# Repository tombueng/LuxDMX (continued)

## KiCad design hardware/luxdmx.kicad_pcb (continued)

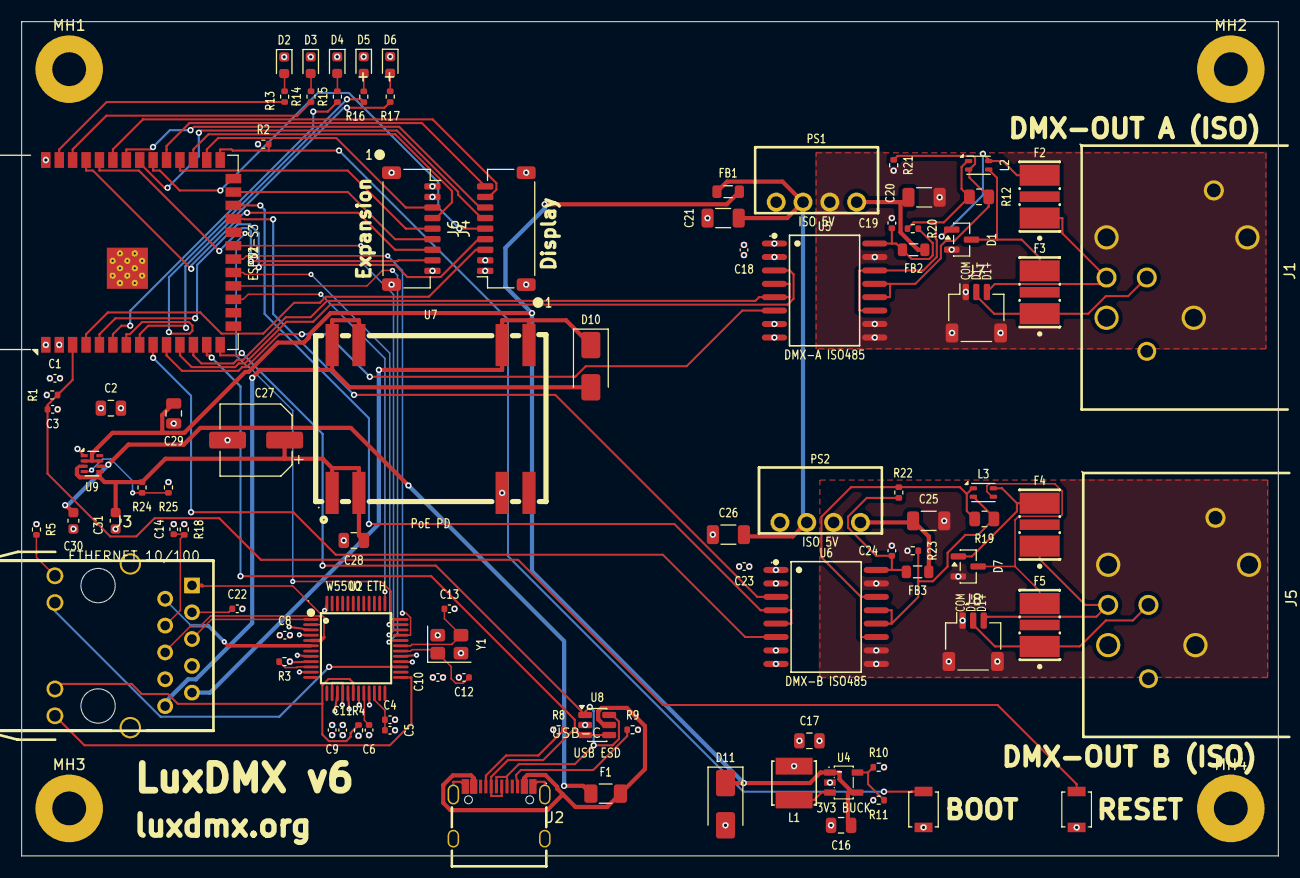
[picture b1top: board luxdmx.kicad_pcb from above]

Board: 4 copper layers, 119.0 x 79.0 mm, 97 parts (0 on the bottom side), 86 nets.

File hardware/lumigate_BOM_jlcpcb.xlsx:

Comment | Designator | Footprint | LCSC Part #
100nF 0402 | C1,C5,C8,C9,C10,C11,C14,C15,C18,C19,C22,C23,C24 | C_0402_1005Metric | C1525
10uF 0805 | C2,C28 | C_0805_2012Metric | C15850
1uF 0402 (EN power-on RC) | C3,C4 | C_0402_1005Metric | C52923
4.7uF 0402 | C6 | C_0402_1005Metric | C23733
22pF 0402 | C12,C13 | C_0402_1005Metric | C1555
22uF 0805 | C16,C17,C29 | C_0805_2012Metric | C45783
10uF 1206 | C20,C21,C25,C26 | C_1206_3216Metric | C13585
100uF 25V SMD electrolytic (PoE output bulk) | C27 | CP_Elec_6.3x7.7 | C970685
1uF 0603 (TPS2116 VIN1 input cap) | C30,C31 | C_0603_1608Metric | C15849
SM712 TVS SOT-23 | D1,D7 | SOT-23 | C404012
LED red 0603 | D2 | LED_0603_1608Metric | C2286
LED green 0603 KT-0603G | D3 | LED_0603_1608Metric | C12624
LED yellow 0603 NCD0603Y2 | D4 | LED_0603_1608Metric | C89811
LED blue 0603 KT-0603B | D5 | LED_0603_1608Metric | C2288
LED white 0603 | D6 | LED_0603_1608Metric | C2290
SMAJ58A TVS SMA (rectified-PoE surge clamp) | D10 | D_SMA | C110521
SMAJ5.0A TVS SMA (+5V transient clamp) | D11 | D_SMA | C151932
BSMD1206-150-16V 1.5A/16V resettable PPTC fuse (USB VBUS) | F1 | Fuse_1206_3216Metric | C883133
600R@100MHz ferrite bead 0805 (+5V to DMX DC-DC) | FB1,FB2,FB3 | L_0805_2012Metric | C139168
Neutrik NC5FAH XLR-5 female horizontal PCB (E1.11 DMX out) | J1,J5 | CONN-TH_NC5FAH | C368501
USB-C data (TYPE-C-31-M-12) | J2 | USB-C_SMD-TYPE-C-31-M-12_1 | C165948
RJ45 MagJack HY931147C PoE 10/100 (integrated rectifier + magnetics) | J3 | RJ45-TH_HY931147C | C91754
JST SH 1.0mm 9-pin SMD SM09B-SRSS-TB (optional display; pre-crimped cables) | J4,J6 | JST_SH_SM09B-SRSS-TB_1x09-1MP_P1.00mm_Horizontal | C160408
JST SH 1.0mm 3-pin SMD SM03B-SRSS-TB (DMX-A breakout) | J7,J8 | JST_SH_SM03B-SRSS-TB_1x03-1MP_P1.00mm_Horizontal | C160403
2.2uH power inductor (CKCS4030) | L1 | IND-SMD_L4.0-W4.0 | C354584
ACM2012-201-2P common-mode choke (DMX-A pair) | L2,L3 | L_CommonModeChoke_Coilank_ACM2012 | C383338
B0505S-1W iso DC-DC (EVISUN) | PS1,PS2 | PWRM-TH_B0505S-1W | C7465127
MMBT3904 SOT-23 | Q1,Q2 | SOT-23 | C20526
10k 0402 | R1,R2,R6,R7,R11 | R_0402_1005Metric | C25744
12k 0402 W5500 EXRES1 (12.4k spec OOS at LCSC; 12k within 100BASE-TX +-5%) | R3 | R_0402_1005Metric | C25752
330R 0402 | R4,R5 | R_0402_1005Metric | C25104
5k1 0402 | R8,R9 | R_0402_1005Metric | C25905
45.3k 0402 1% (buck FB top -> 3.32V) | R10 | R_0402_1005Metric | C137977
120R 0805 (DMX-A termination) | R12,R19 | R_0805_2012Metric | C17437
1k 0402 | R13,R15 | R_0402_1005Metric | C11702
150R 0402 | R14,R16,R17 | R_0402_1005Metric | C25082
49.9R 1% 0402 W5500 TX center-tap bias | R18 | R_0402_1005Metric | C25120
tact sw B3U-1000P | SW1,SW2 | SW_SPST_B3U-1000P | C231329
ESP32-S3-WROOM-1-N8 (8MB) | U1 | ESP32-S3-WROOM-1 | C2913198
W5500 SPI Ethernet | U2 | LQFP-48_L7.0-W7.0-P0.50-LS9.0-BL | C32843
CH340C USB-UART | U3 | SOP-16_L10.0-W3.9-P1.27-LS6.0-BL | C84681
SY8089 buck 5->3.3V | U4 | SOT-23-5_L3.0-W1.7-P0.95-LS2.8-BR | C78988
ISO3086DWR isolated RS-485 | U5,U6 | SOIC-16_L10.3-W7.5-P1.27-LS10.3-BL | C183095
DP9900M-5V PoE PD + isolated DC-DC module (802.3af) | U7 | PWRM-SMD_DP9900M-5V | C5380106
USBLC6-2SC6 USB ESD/TVS array (SOT-23-6) | U8 | SOT-23-6 | C7519
TPS2116DRLR ideal-diode power mux (USB/PoE 5V OR-ing) | U9 | SOT-583-8 | C3235557
25MHz crystal 2520 | Y1 | Crystal_SMD_2520-4Pin_2.5x2.0mm | C2981622

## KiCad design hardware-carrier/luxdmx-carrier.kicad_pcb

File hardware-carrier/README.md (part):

# LuxDMX carrier board

A 2-layer PCB for off-the-shelf modules: an ESP32-S3 dev board, up to three RS-485 modules, a
W5500 Ethernet module and an OLED. Encoder and two buttons sit on the board itself. DMX and RDM on
up to three ports, WS281x pixels on up to five.

The board is built and runs on the bench; most firmware testing happens on it.

| | |
|---|---|
| Board | 100 x 80 mm, 2 layers, 1 oz copper, no mounting holes |
| DMX / RDM | up to 3 ports, one MAX3485 module each, direction pin driven, **not isolated** |
| Pixels | up to 5 WS281x ports, buffered to 5 V by a 74HCT541 |
| Network | WiFi, or wired with a W5500 module |
| Logic supply | USB-C on the ESP module, external 5 V, or a buck module off the pixel rail |
| Pixel supply | 12 or 24 V screw terminal, fused on the board, 9.8 A max |
| UI | 1.3" SH1106 OLED, EC11 encoder with push switch, two buttons |
| Firmware | **ESP32-S3 + PSRAM** image, then the **LuxDMX Carrier** board in `/config` |

Contents: [Modules](#modules) · [Pin map](#pin-map) · [Power](#power) · [DMX ports](#dmx-ports) ·
[Pixel ports](#pixel-ports) · [All parts](#all-parts) · [Build levels](#build-levels) ·
[Ordering](#ordering) · [Assembly](#assembly) · [Before you power it](#before-you-power-it) ·
[Firmware](#firmware) · [Known issues](#known-issues)

## Modules

These are the units the bench board is built with. Other sellers' modules work if pinout and
size match, check both before buying.

| Slot | Module | Pins | Notes |
|---|---|---|---|
| MCU | ESP32-S3-DevKitC-1 clone, **WROOM-1-N16R8**, dual USB-C (Binghe, Amazon.de B0D6B2CYNW). Search `ESP32-S3-DevKitC-1 N16R8` | 2 x 22, official DevKitC-1 pin order | 57.5 x 27.9 mm, rows **25.40 mm** apart. Espressif's own DevKitC-1 has 22.86 mm rows and does **not** fit. Compare the seller's drawing against the footprint before buying |
| RS-485, x3 | MAX3485 module, silk `RS485 V2.01` (RAKSTORE, Amazon.de B0C2HRQ393). Search `MAX3485 TTL to RS485 module 3.3V` | left: GND / A / B<br>right: EN / VCC / RXD / TXD / GND | 3.3 V, not isolated. EN is DE and RE tied together, one GPIO per port, which is what RDM needs. A module without EN can't do RDM. RXD is the module's input (DI), TXD its output (RO); the board crosses them |
| Ethernet | USR-ES1 (W5500). Search `USR-ES1 W5500` | 2 x 6, rows 20.32 mm | 3.3 V only, no LDO on the module. About 132 mA typical. The single-row 8-pin W5500 boards are a different module |
| Display | 1.3" OLED, SH1106, 128 x 64, I2C. Search `1.3 inch OLED I2C SH1106` | board pads 1-4: GND / 3V3 / SCL / SDA | Sits on a 1x4 female socket, 8.5 mm tall, which lifts the glass 10.9 mm clear of the modules. Sold with VCC and GND in either order, read the module's silk |
| Encoder | bare EC11 with push switch, 20 mm D-shaft (the part inside a KY-040) | soldered to the board | GPIO pull-ups are internal, the KY-040's three 10k aren't needed |
| Buttons, x2 | 6 x 6 mm tact switch | soldered to the board | Plunger 5 to 30 mm on the same land. The encoder shaft stands 20 mm, so 30 mm reaches the same front panel |

## Pin map

From the board's nets. Picking **LuxDMX Carrier** in `/config` sets these.

| Function | GPIO |
|---|---|
| DMX 1 TX / RX / DE+RE | 17 / 18 / 16 |
| DMX 2 TX / RX / DE+RE | 15 / 7 / 6 |
| DMX 3 TX / RX / DE+RE | 5 / 4 / 8 |
| W5500 SCLK / MOSI / MISO / CS / INT / RST | 12 / 11 / 13 / 10 / 14 / 9 |
| Pixel 1 / 2 / 3 / 4 / 5 data (before the buffer) | 38 / 39 / 40 / 47 / 48 |
| Display SDA / SCL | 1 / 2 |
| Encoder A / B / switch | 42 / 41 / 21 |
| Button 1 / 2 (to GND) | 3 / 46 |
| `EXP` header | 3V3, GND, 47, 48, 43 (TX0), 44 (RX0) |

Not used, and not usable: 35/36/37 (octal PSRAM on any R8 module), 45 (flash voltage strap), 19/20
(USB), 0 (BOOT). IO48 also drives the module's own RGB LED, see [pixel ports](#pixel-ports).

## Power

### Rails

| Net | Comes from | Feeds |
|---|---|---|
| `+5V` | USB-C on the ESP module, **or** the `5V IN` header, **or** the buck module | ESP module 5V pin, 74HCT541 |
| `+3V3` | the ESP module's own regulator (800 mA on Espressif's design) | ESP32-S3, MAX3485 x3, W5500, OLED, DMX bias, pull-ups |
| `V_PIX_IN` | `12-24V IN` screw terminal | the fuse |
| `V_PIX` | after the fuse | 1000 µF, V+ on all five pixel terminals, buck module input |
| `GND` | one common ground | everything, including DMX pin 1 (the ports are not isolated) |

The 3.3 V load with everything fitted is about 269 mA. The W5500 and WiFi don't run at the same time.

No ORing diodes between the three 5 V sources: **one at a time**. With the buck fitted, don't plug
in USB while the 12/24 V is on.

### Supply setups

| Setup | Fit | Logic from | Pixel rail |
|---|---|---|---|
| DMX only, bench | nothing | USB-C | unused |
| DMX only, in a box | `5V IN` header | external 5 V | unused |
| Pixels, two supplies | 12-24V terminal, fuse, 1000 µF | USB or `5V IN` | 12/24 V |
| Pixels, one supply | as above + buck module | buck, from `V_PIX` | 12/24 V |
| 5 V pixels | 12-24V terminal, fuse, 1000 µF, no buck | USB or `5V IN` | 5 V |

### 5 V pixels and USB

**USB never reaches the pixel terminals.** `V+` on all five is `V_PIX`, and `V_PIX` only comes from
the `12-24V IN` terminal through the fuse. Neither USB nor `5V IN` is connected to it. With nothing on
that terminal the data is there, `/pixels.json` shows the port running at full frame rate, and the
strip stays dark.

**WS2812 and other 5 V pixels:** the 5 V goes into `12-24V IN`, despite the name. The rail doesn't
care about the voltage. Leave the buck out, it can't make 5 V out of 5 V.

**One 5 V supply for both:** bridge `5V IN` to `12-24V IN`. That's how the bench carrier runs. The
bridge also ties the logic to whatever is on that terminal, so take it off before anything above 5 V
gets near the board, and leave USB unplugged while it's on (one 5 V source at a time).

**USB may not even reach `+5V`.** The pixel buffer runs on `+5V`, and USB only gets there through the
module's 5V pin. On some S3 modules that pin isn't connected to USB until the `IN-OUT` solder pads are
bridged. We haven't measured this on a module yet, but the bench carrier points that way: on USB, even
with `5V IN` bridged to `12-24V IN`, its pixels stayed dark, and a real 5 V supply on that bridge lit
them. If you run from USB, check for 5 V on `5V IN` with a meter. If it's missing, the ESP runs and
every pixel port is silent, because the buffer has no supply.

### Fuse

Exactly one of these three:

| Option | Part | When |
|---|---|---|
| Polyfuse | Bourns MF-R500 (30 V, 5 A hold, 10 A trip), LCSC C208489 | default. Resets itself after cooling |
| Blade fuse | Keystone 3568 holder, MINI blade fuses (ATM, Littelfuse 297/997) | you'd rather swap a fuse. Not ATO/ATC, those are twice as wide |
| Solder bridge | pad pair on the back, inside the polyfuse footprint | the supply lead already has a fuse |

Polyfuse land: three holes, 5.08 mm (middle, MF-R110 to MF-R400, up to 4 A) and 10.2 mm (right,
MF-R500, up to 9 A). Use **30 V** parts only. MF-RHT, MF-RG and anything else rated 16 V is out of
rating at 24 V the moment it trips. MF-R900 (24 mm body) hits the 1000 µF can. Equivalents to the
MF-R500: ECE RB500-30, Littelfuse RUEF500. Full list in [`production/BOM.md`](production/BOM.md).

Never polyfuse and bridge together.

### Buck module

MP1584EN step-down module. Input max **28 V**, so a 24 V supply must not idle above that. **Set it to
5.0 V before soldering it in**: they ship with the trimmer anywhere, and 12 V on `+5V` kills the ESP32,
the W5500 and the display. Input is `V_PIX`, so it sits behind the fuse.

The land is four 12 x 5 mm pads with a solder-mask grid (7 x 3 windows of 1.1 mm), so modules from
22 x 18 to 30 x 18 mm land. LM2596 modules (43 x 21 mm) do not fit.

### Current rating

The pixel supply runs as 4.8 mm tracks from the inlet through the fuse along the terminal row. Each
output gets the full width and its own 4.8 mm GND return.

| 1 oz copper | 10 K rise | 20 K rise | at 24 V |
|---|---:|---:|---:|
| Pixel rail, fuse to the outputs | 7.2 A | **9.8 A** | 170 - 235 W |
| Pixel rail, inlet to the fuse | 7.3 A | 9.9 A | |
| Any single output | 7.2 A | 9.8 A | |
| GND return per output | 7.4 A | 10.1 A | |
| GND pour overall | 46.3 A | 62.8 A | |

- 10 K: board stays hand-warm. 20 K: fine for FR4, more current. Neither is a safety limit.
- All five ports in use: about 2 A each. A 5 m WS2815 run is about 5 A at full white.
- More than that: inject power at the strip.
- The polyfuse bridge pads limit a fuse-less build to 8.8 A. Bridge the through-holes with a wire for more.
- The bulk cap and buck hang off 2.0 mm spurs (5.3 A), they aren't load paths.

### Decoupling

| Where | Parts |
|---|---|
| 3.3 V at the ESP module | 100 nF + 22 µF |
| W5500, under the module on the back | 100 nF / 1 µF / 22 µF, smallest closest to its 3V3 pin |
| Pixel rail | 1000 µF 35 V, 13 mm can, 5.0 mm pitch |

The W5500 set matters: the 3.3 V reaches it through 62 mm of 0.60 mm track (about 62 nH), so the
local 22 µF is what holds the rail when the PHY steps its load.

## DMX ports

Per port, on the board:

| Part | Connection | Purpose |
|---|---|---|
| MAX3485 module | EN, DI, RO from the pin map | transceiver, 3.3 V |
| 10k | DE+RE to GND | driver off, receiver on while the ESP boots. Without it the driver can key the bus before firmware runs |
| 120 Ω | A to B | termination. Only at the **end** of the bus, and only if the module doesn't already have one |
| 330 Ω | A to 3.3 V | fail-safe bias |
| 330 Ω | B to GND | fail-safe bias, always as a pair with the one above |
| 2 x TVS | A to GND, B to GND | surge clamp for ports that leave the box |
| 3-pin header | 1 GND, 2 B, 3 A | to XLR pin 1 / 2 / 3 |

Bias: RS-485 wants more than 200 mV idle. 330 Ω gives 508 mV with one terminator and 275 mV with two.
270 to 390 Ω are fine, 430 and 470 Ω marginal, 560 Ω and up not enough. Fit it once per bus. Many
MAX3485 modules already carry 120 Ω and bias resistors; check before adding a second set.

TVS: SMF12CA (SOD-123FL, 200 W), or SMAJ12CA (SMA, 400 W). 12 V standoff so it stays off at the
+12 V common mode RS-485 allows, 14.7 V breakdown, 19.9 V clamp at 10 A. A varistor is no
substitute, it clamps around 40 V.

Header: 2.54 mm pitch, 1.20 mm holes. Takes a pin header or a 2.54 mm screw terminal (Phoenix
MPT 0,5/3-2,54, TE 282834-3, Xinya XY308-2.54-3P).

**Not isolated.** DMX GND is board GND. Fine for a desk or a small rig. Use an isolated RS-485
module on a separate build if you need it.

## Pixel ports

```
GPIO 38/39/40/47/48 ── 74HCT541 (5 V) ── 330 Ω ── terminal DATA
                                         V_PIX ── terminal V+
                                           GND ── terminal GND
```

**The buffer is required for pixels.** WS281x need 0.7 x VDD = 3.5 V as logic high on a 5 V strip
input; the S3 gives 3.3 V. Without the buffer nothing reaches the terminals at all, they hang off its
outputs.

### The buffer chip

`74HCT541D,653` (Nexperia), LCSC C547781, about 0.42 EUR. VCC on `+5V`, both output enables tied to
GND, inputs A1 to A5 used, A6 to A8 (pins 7 to 9) tied to GND by a track to pin 10.

Two things decide the part:

1. **The T.** HCT, AHCT and ACT have TTL input thresholds (VIH 2.0 V), so 3.3 V switches them on a
   5 V supply. HC, AHC and AC need 3.5 V and don't switch reliably.
2. **The package.** The land is SOIC-20W: 1.27 mm pitch, rows 10.10 mm apart, pads extended 0.80 mm
   for a soldering iron.

| Fits | Doesn't fit |
|---|---|
| 74HCT541D (Nexperia) | 74HC541, 74AHC541, 74AC541: CMOS thresholds |
| 74AHCT541D (Nexperia) | 74HCT540 / 74AHCT540: inverting, same pinout |
| SN74AHCT541DW, SN74HCT541DW (TI) | 74HCT244: different pinout |
| CD74ACT541M (TI) | `...541PW` (TSSOP 0.65 mm), what LCSC stocks most of |
| | `...541DB`, `...541DGS`, `...541RKS`, `SN74AHCT541NS` (narrow SO-20), DIP |
| | 74LVC541A: can't output 5 V |

### Series resistors

330 Ω per port at the buffer output. The buffer switches in 3 to 5 ns into unterminated strip wire;
that edge rings and overshoots into the first LED. A WS281x bit is 1.25 µs, so the slower edge
costs nothing. The resistor also limits current if DATA meets 5 V or GND. 220 to 470 Ω all work.
Same part as the DMX bias resistors.

### Terminals

5.08 mm, 3 pole: V+ / DATA / GND. Pads 3.60 x 3.30 mm on 1.30 mm holes. Fit the terminal or solder
the wire flat onto the pad.

### Things to know

- **IO48 is pixel port 5 and the module's RGB LED.** The carrier preset turns the status LED off.
  Not using port 5? Status LED back on at GPIO48, WS2812.
- **EXP header** brings out IO47 and IO48 **unbuffered** (3.3 V), alongside the buffered ports 4 and 5.
- **5 V strip works.** The rail is a pass-through and doesn't care about voltage, but 5 V strip needs
  about 3.5 times the current of 12 V strip for the same pixels. The limit here is amps, so the
  firmware defaults to WS2815 (12 V).
- **Driver:** the firmware uses the S3's LCD_CAM peripheral when PSRAM is there, which is why the
  carrier wants the PSRAM image. Chips, universes, power caps: [`docs/pixels.md`](../docs/pixels.md).

### Data line return path

341 mm of data line on the board. Two layers can't give every millimetre a ground plane underneath:

| | |
|---|---:|
| ground directly opposite, other layer | 60 % |
| ground alongside within 1.5 mm | 31 % |
| no ground within reach | 9 % |

The 9 % is 29 mm where the lines cross the supply bus, plus 8.5 mm under the ESP module. For a few
metres of strip this doesn't matter, and the series resistors cover it.

## All parts

Everything that can go on the board. Only the ESP module is mandatory. Small parts are 1206 in the
BOM, the lands take 0402 to 1206.

### Core

| Part | Value / part number | Fit when |
|---|---|---|
| ESP32-S3 module | DevKitC-1 clone, N16R8, 25.40 mm rows | always |

### DMX, per port (x3)

| Part | Value / part number | LCSC | Fit when |
|---|---|---|---|
| RS-485 module | MAX3485, with EN pin | | port used |
| DMX header | 1x3 pin header, or 2.54 mm screw terminal | | port used |
| `10k dir` | 10k, 1206W4F1002T5E | C17902 | port used |
| `120R term` | 120 Ω, 1206W4F1200T5E | | port at the end of the bus, module has none |
| `330R bias+`, `330R bias-` | 330 Ω, 1206W4J0331T5E | C25374 | port drives the bus, once per bus |
| `TVS bidir` x2 | SMF12CA, or SMAJ12CA | C353317 | port leaves the enclosure |

### Pixels

| Part | Value / part number | LCSC | Fit when |
|---|---|---|---|
| `74AHCT541 pixel buffer` | 74HCT541D,653, SO-20 300 mil | C547781 | at least one pixel port used |
| `330R PIX1..5` | 330 Ω, 1206W4J0331T5E | C25374 | that port used |
| `Pixel1..5` | KF128-5.08-3P screw terminal | C474953 | that port used |
| `12-24V IN` | KF128-5.08-2P screw terminal, 24 A | C474952 | any pixel port used |
| `1000uF 35V` | KM108M035J20RR0VH2FP0, D13 x 20 mm | C10749 | any pixel port used |
| Fuse | MF-R500 polyfuse **or** Keystone 3568 blade holder **or** solder bridge | C208489 (MF-R500) | any pixel port used, see [Fuse](#fuse) |

### Supply

| Part | Value / part number | Fit when |
|---|---|---|
| `5V Buck Converter` | MP1584EN module, set to 5.0 V first | logic from 12/24 V, no USB, no `5V IN` |
| `5V IN` | 1x2 pin header | external 5 V instead of USB |
| `100nF` | 100 nF X7R, CL31B104KBCNNNC (C24497) | recommended |
| `22uF 3V3 bulk` | 22 µF 6.3 V X5R, CL31A226MQHNNNE (C159757) | recommended |

### Network

| Part | Value / part number | LCSC | Fit when |
|---|---|---|---|
| `W5500 Ethernet Module` | USR-ES1 | | wired Ethernet |
| `10k ETH_CS pu` | 10k to 3.3 V | C17902 | W5500 fitted. Holds CS high while the GPIOs float during reset |
| `10k ETH_RST pu` | 10k to 3.3 V | C17902 | W5500 fitted. Without it the W5500 resets itself during boot |
| `100nF W5500` | 100 nF | C24497 | W5500 fitted |
| `1uF W5500` | 1 µF X7R, CL31B105KBHNNNE | C1848 | W5500 fitted |
| `22uF W5500` | 22 µF X5R | C159757 | W5500 fitted |

### Interface

| Part | Value / part number | Fit when |
|---|---|---|
| `Display` | 1.3" SH1106 I2C OLED on a 1x4 female socket, 8.5 mm | you want the display |
| `Encoder` | EC11 with push switch, 20 mm D-shaft | you want the on-unit menu |
| `Button 1`, `Button 2` | 6 x 6 mm tact switch, 30 mm plunger | you want the buttons |
| `EXP` | 1x6 pin header | you need spare pins |

LCSC small parts for a fully fitted board: about 2.80 EUR. Stock, prices, marketplace links and
search terms for every module: [`production/BOM.md`](production/BOM.md). Every position with its
side and fit condition: [`ASSEMBLY.md`](ASSEMBLY.md).

## Build levels

| Build | DMX | Pixels | Network | Fit |
|---|---|---|---|---|
| DMX only, USB powered | 1-3 | - | WiFi | ESP, RS-485 module + header + 10k per port, bias / termination / TVS as needed |
| DMX + LAN | 1-3 | - | W5500 | above + W5500, its two 10k and 100 nF / 1 µF / 22 µF |
| Pixels only | - | 1-5 | WiFi | ESP, buffer, 330 Ω + terminal per port, 1000 µF, inlet, fuse, buck or USB |
| Everything | 3 | 5 | W5500 | all of it, plus display, encoder, buttons |

## Ordering

- **PCB:** [`production/luxdmx-carrier-gerbers.zip`](production/), 2 layers, 1 oz, 1.6 mm, any fab
  (e.g. <https://cart.jlcpcb.com/quote>).
- **Small parts:** [`production/BOM-LCSC-upload.csv`](production/) goes straight into
  <https://www.lcsc.com/bom>. Also as `BOM.csv` / `BOM.xlsx`, and `BOM-TME.md` for TME.
- **Modules:** search terms and example links in [`production/BOM.md`](production/BOM.md). Links rot,
  search terms don't.

## Assembly

1. Back side first: all small parts sit under the modules.
2. Then the headers and sockets on the front.
3. Set the buck to 5.0 V, then solder it.
4. Plug in the modules.

Hand soldering only. Resistor and capacitor lands run 0.30 to 2.30 mm off centre, so 0402, 0603,
0805 and 1206 all land on copper (1210 overhangs in width). TVS lands go to 2.90 mm and take
SOD-123, SOD-123F, SOD-123FL, SMA and 1206. The lands are longer than the parts and nothing
self-aligns, so this board doesn't reflow.

## Before you power it

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
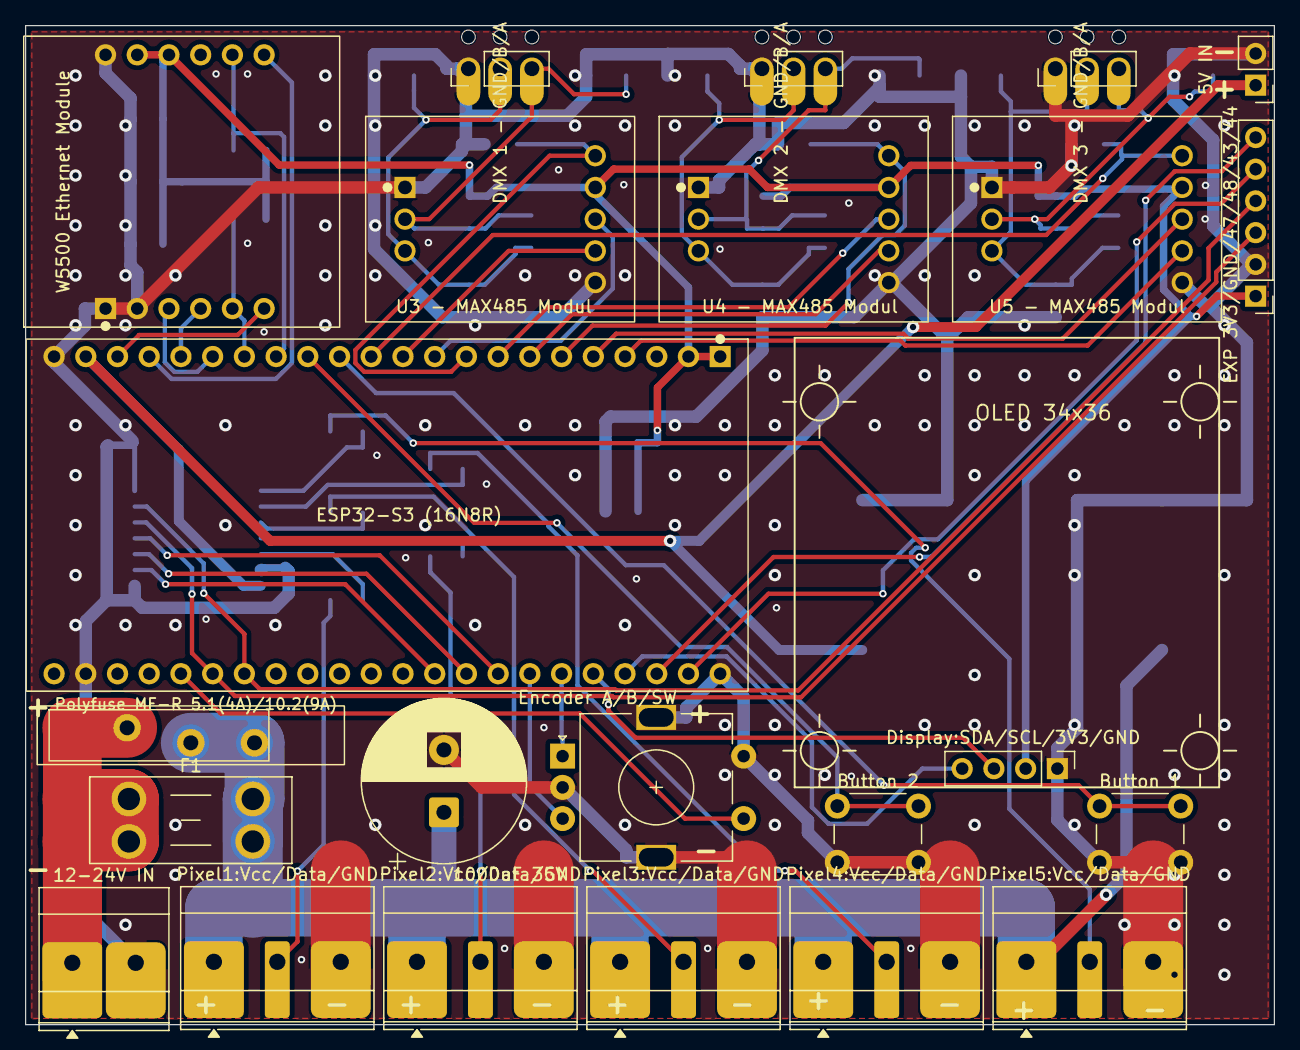
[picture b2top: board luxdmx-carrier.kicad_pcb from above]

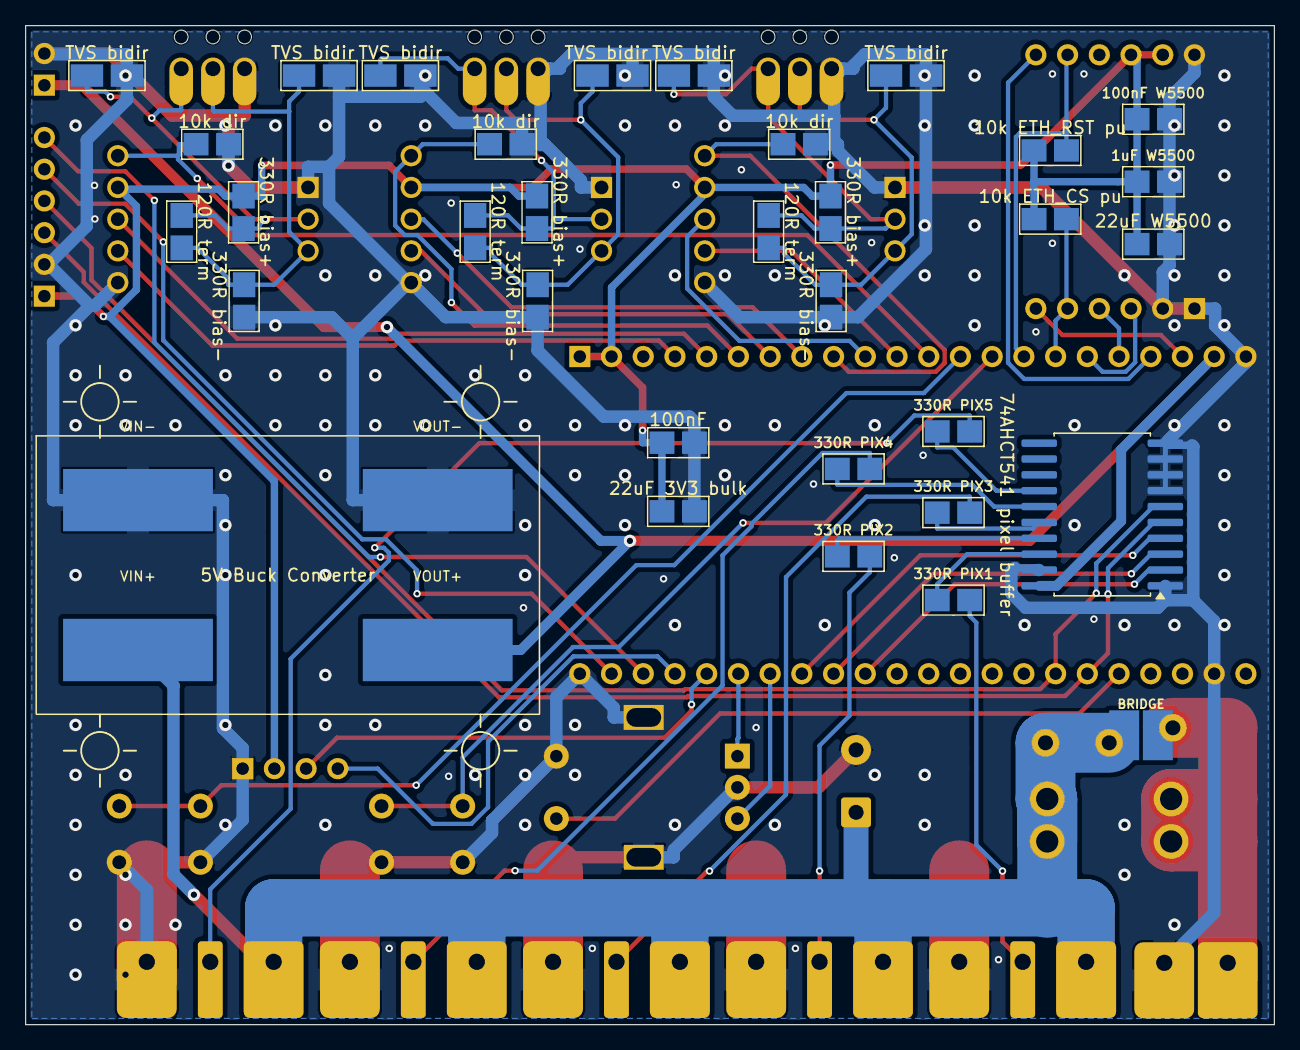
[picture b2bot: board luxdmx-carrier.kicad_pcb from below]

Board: 2 copper layers, 100.0 x 80.0 mm, 55 parts (32 on the bottom side), 50 nets.

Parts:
1uF W5500: 1uF; chip-universal
5V Buck Converter: 12-24V -> 5V buck; buck-module-universal
5V IN: 5V in; PinHeader_1x02_P2.54mm_Vertical
10k ETH_CS pu: 10k ETH_CS pu; chip-universal
10k ETH_RST pu: 10k ETH_RST pu; chip-universal
10k dir, 10k dir#2, 10k dir#3: 10k dir; chip-universal
12-24V IN: 12-24V IN 24A; terminal-1x02-P5.08-bigpad
22uF 3V3 bulk: 22uF 3V3 bulk; chip-universal
22uF W5500: 22uF W5500; chip-universal
74AHCT541 pixel buffer: 74AHCT541 pixel buffer; SOIC-20W_7.5x12.8mm_P1.27mm
100nF, 100nF W5500: 100nF; chip-universal
120R term, 120R term#2, 120R term#3: 120R term; chip-universal
330R PIX1, 330R PIX2, 330R PIX3, 330R PIX4, 330R PIX5: 330R pixel; chip-universal
330R bias+, 330R bias+#2, 330R bias+#3: 330R bias+; chip-universal
330R bias-, 330R bias-#2, 330R bias-#3: 330R bias-; chip-universal
1000uF 35V: 1000uF 35V; CP_Radial_D13.0mm_P5.00mm
Button 1, Button 2: Tact 6x6 H30; SW_PUSH_6mm
DMX 1 - GND/B/A: XLR1 1=shld 2=D- 3=D+; header-1x03-P2.54-terminal
DMX 2 - GND/B/A: XLR2 1=shld 2=D- 3=D+; header-1x03-P2.54-terminal
DMX 3 - GND/B/A: XLR3 1=shld 2=D- 3=D+; header-1x03-P2.54-terminal
Display:SDA/SCL/3V3/GND: OLED SDA/SCL/VCC/GND; PinHeader_1x04_P2.54mm_Vertical
ESP32-S3 (16N8R): ESP32-S3 N16R8; desk_binghe-esp32-s3-devkitc1-n16r8-usbc
EXP 3V3/GND/47/48/43/44: EXP 3V3/GND/47/48/43/44; PinHeader_1x06_P2.54mm_Vertical
Encoder A/B/SW: EC11; encoder-ec11-switch
F1: Blade fuse holder, alternative to the polyfuse; Fuseholder_Blade_Mini_Keystone_3568
Pixel1:Vcc/Data/GND: PIX1 V+/DATA/GND; terminal-1x03-P5.08-bigpad
Pixel2:Vcc/Data/GND: PIX2 V+/DATA/GND; terminal-1x03-P5.08-bigpad
Pixel3:Vcc/Data/GND: PIX3 V+/DATA/GND; terminal-1x03-P5.08-bigpad
Pixel4:Vcc/Data/GND: PIX4 V+/DATA/GND; terminal-1x03-P5.08-bigpad
Pixel5:Vcc/Data/GND: PIX5 V+/DATA/GND; terminal-1x03-P5.08-bigpad
Polyfuse MF-R 5.1(4A)/10.2(9A): MF-R 30V: links+mitte bis 4A, links+rechts bis 9A; polyfuse-dual-pitch
TVS bidir: TVS bidir; chip-universal-tvs
TVS bidir#2, TVS bidir#3, TVS bidir#4, TVS bidir#5, TVS bidir#6: TVS bidir; chip-universal-tvs
U3 - MAX485 Modul: MAX3485 DMX1; desk_rakstore-max3485
U4 - MAX485 Modul: MAX3485 DMX2; desk_rakstore-max3485
U5 - MAX485 Modul: MAX3485 DMX3; desk_rakstore-max3485
W5500 Ethernet Module: USR-ES1 W5500; usr-es1-w5500

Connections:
+3V3: 1uF W5500.1, 10k ETH_CS pu.1, 10k ETH_RST pu.1, 22uF 3V3 bulk.1, 22uF W5500.1, 100nF.1, 100nF W5500.1, 330R bias+.1, 330R bias+#2.1, 330R bias+#3.1, Display:SDA/SCL/3V3/GND.2, ESP32-S3 (16N8R).1, ESP32-S3 (16N8R).2, EXP 3V3/GND/47/48/43/44.1, U3 - MAX485 Modul.5, U4 - MAX485 Modul.5, U5 - MAX485 Modul.5, W5500 Ethernet Module.8, W5500 Ethernet Module.9
+5V: 5V Buck Converter.4, 5V IN.1, 74AHCT541 pixel buffer.20, ESP32-S3 (16N8R).21
BTN1: Button 1.1, ESP32-S3 (16N8R).13
BTN2: Button 2.1, ESP32-S3 (16N8R).14
DMX1_A: 120R term#2.1, 330R bias+#2.2, DMX 1 - GND/B/A.3, TVS bidir#3.1, U3 - MAX485 Modul.2
DMX1_B: 120R term#2.2, 330R bias-#2.1, DMX 1 - GND/B/A.2, TVS bidir#6.1, U3 - MAX485 Modul.3
DMX1_DIR: 10k dir.1, ESP32-S3 (16N8R).9, U3 - MAX485 Modul.4
DMX1_RX: ESP32-S3 (16N8R).11, U3 - MAX485 Modul.7
DMX1_TX: ESP32-S3 (16N8R).10, U3 - MAX485 Modul.6
DMX2_A: 120R term#3.1, 330R bias+#3.2, DMX 2 - GND/B/A.3, TVS bidir#4.1, U4 - MAX485 Modul.2
DMX2_B: 120R term#3.2, 330R bias-.1, DMX 2 - GND/B/A.2, TVS bidir.1, U4 - MAX485 Modul.3
DMX2_DIR: 10k dir#2.1, ESP32-S3 (16N8R).6, U4 - MAX485 Modul.4
DMX2_RX: ESP32-S3 (16N8R).7, U4 - MAX485 Modul.7
DMX2_TX: ESP32-S3 (16N8R).8, U4 - MAX485 Modul.6
DMX3_A: 120R term.1, 330R bias+.2, DMX 3 - GND/B/A.3, TVS bidir#2.1, U5 - MAX485 Modul.2
DMX3_B: 120R term.2, 330R bias-#3.1, DMX 3 - GND/B/A.2, TVS bidir#5.1, U5 - MAX485 Modul.3
DMX3_DIR: 10k dir#3.1, ESP32-S3 (16N8R).12, U5 - MAX485 Modul.4
DMX3_RX: ESP32-S3 (16N8R).4, U5 - MAX485 Modul.7
DMX3_TX: ESP32-S3 (16N8R).5, U5 - MAX485 Modul.6
ENC_A: ESP32-S3 (16N8R).28, Encoder A/B/SW.A
ENC_B: ESP32-S3 (16N8R).29, Encoder A/B/SW.B
ENC_SW: ESP32-S3 (16N8R).40, Encoder A/B/SW.S1
ETH_CS: 10k ETH_CS pu.2, ESP32-S3 (16N8R).16, W5500 Ethernet Module.5
ETH_INT: ESP32-S3 (16N8R).20, W5500 Ethernet Module.6
ETH_MISO: ESP32-S3 (16N8R).19, W5500 Ethernet Module.12
ETH_MOSI: ESP32-S3 (16N8R).17, W5500 Ethernet Module.3
ETH_RST: 10k ETH_RST pu.2, ESP32-S3 (16N8R).15, W5500 Ethernet Module.11
ETH_SCK: ESP32-S3 (16N8R).18, W5500 Ethernet Module.4
EXP_IO43: ESP32-S3 (16N8R).24, EXP 3V3/GND/47/48/43/44.5
EXP_IO44: ESP32-S3 (16N8R).25, EXP 3V3/GND/47/48/43/44.6
GND: 1uF W5500.2, 5V Buck Converter.1, 5V Buck Converter.3, 5V IN.2, 10k dir.2, 10k dir#2.2, 10k dir#3.2, 12-24V IN.2, 22uF 3V3 bulk.2, 22uF W5500.2, 74AHCT541 pixel buffer.1, 74AHCT541 pixel buffer.7, 74AHCT541 pixel buffer.8, 74AHCT541 pixel buffer.9, 74AHCT541 pixel buffer.10, 74AHCT541 pixel buffer.19, 100nF.2, 100nF W5500.2, 330R bias-.2, 330R bias-#2.2, 330R bias-#3.2, 1000uF 35V.2, Button 1.2, Button 2.2, DMX 1 - GND/B/A.1, DMX 2 - GND/B/A.1, DMX 3 - GND/B/A.1, Display:SDA/SCL/3V3/GND.1, ESP32-S3 (16N8R).22, ESP32-S3 (16N8R).23, ESP32-S3 (16N8R).43, EXP 3V3/GND/47/48/43/44.2, Encoder A/B/SW.C, Encoder A/B/SW.MP, Encoder A/B/SW.S2, Pixel1:Vcc/Data/GND.3, Pixel2:Vcc/Data/GND.3, Pixel3:Vcc/Data/GND.3, Pixel4:Vcc/Data/GND.3, Pixel5:Vcc/Data/GND.3, TVS bidir.2, TVS bidir#2.2, TVS bidir#3.2, TVS bidir#4.2, TVS bidir#5.2, TVS bidir#6.2, U3 - MAX485 Modul.1, U3 - MAX485 Modul.8, U4 - MAX485 Modul.1, U4 - MAX485 Modul.8, U5 - MAX485 Modul.1, U5 - MAX485 Modul.8, W5500 Ethernet Module.1, W5500 Ethernet Module.2, W5500 Ethernet Module.7
I2C_SCL: Display:SDA/SCL/3V3/GND.3, ESP32-S3 (16N8R).27
I2C_SDA: Display:SDA/SCL/3V3/GND.4, ESP32-S3 (16N8R).26
PIX1: 74AHCT541 pixel buffer.2, ESP32-S3 (16N8R).32
PIX1_5V: 330R PIX1.2, Pixel1:Vcc/Data/GND.2
PIX1_BUF: 74AHCT541 pixel buffer.18, 330R PIX1.1
PIX2: 74AHCT541 pixel buffer.3, ESP32-S3 (16N8R).31
PIX2_5V: 330R PIX2.2, Pixel2:Vcc/Data/GND.2
PIX2_BUF: 74AHCT541 pixel buffer.17, 330R PIX2.1
PIX3: 74AHCT541 pixel buffer.4, ESP32-S3 (16N8R).30
PIX3_5V: 330R PIX3.2, Pixel3:Vcc/Data/GND.2
PIX3_BUF: 74AHCT541 pixel buffer.16, 330R PIX3.1
PIX4: 74AHCT541 pixel buffer.5, ESP32-S3 (16N8R).39, EXP 3V3/GND/47/48/43/44.3
PIX4_5V: 330R PIX4.2, Pixel4:Vcc/Data/GND.2
PIX4_BUF: 74AHCT541 pixel buffer.15, 330R PIX4.1
PIX5: 74AHCT541 pixel buffer.6, ESP32-S3 (16N8R).38, EXP 3V3/GND/47/48/43/44.4
PIX5_5V: 330R PIX5.2, Pixel5:Vcc/Data/GND.2
PIX5_BUF: 74AHCT541 pixel buffer.14, 330R PIX5.1
V_PIX: 5V Buck Converter.2, 1000uF 35V.1, F1.2, Pixel1:Vcc/Data/GND.1, Pixel2:Vcc/Data/GND.1, Pixel3:Vcc/Data/GND.1, Pixel4:Vcc/Data/GND.1, Pixel5:Vcc/Data/GND.1, Polyfuse MF-R 5.1(4A)/10.2(9A).2
V_PIX_IN: 12-24V IN.1, F1.1, Polyfuse MF-R 5.1(4A)/10.2(9A).1

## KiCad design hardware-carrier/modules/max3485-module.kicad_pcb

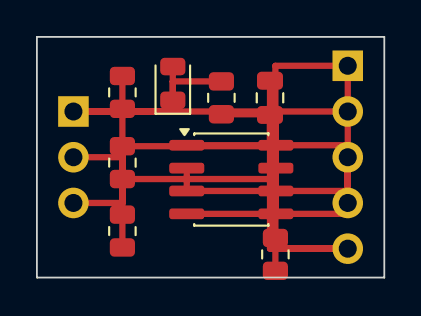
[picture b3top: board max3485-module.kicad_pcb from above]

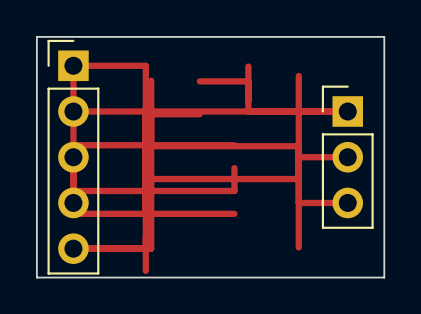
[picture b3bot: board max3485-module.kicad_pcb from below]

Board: 2 copper layers, 19.3 x 13.4 mm, 10 parts (2 on the bottom side), 8 nets.

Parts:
C1: C1; C_0805_2012Metric
D1: D1; LED_0805_2012Metric
J1: J1; PinHeader_1x03_P2.54mm_Vertical
J2: J2; PinHeader_1x05_P2.54mm_Vertical
R1: R1; R_0805_2012Metric
R2: R2; R_0805_2012Metric
R3: R3; R_0805_2012Metric
R4: R4; R_0805_2012Metric
R5: R5; R_0805_2012Metric
U1: U1; SOIC-8_3.9x4.9mm_P1.27mm

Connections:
A: J1.2, R1.2, R2.1, U1.6
B: J1.3, R2.2, R3.1, U1.7
DI: J2.3, U1.4
EN: J2.1, R5.1, U1.2, U1.3
GND: C1.2, D1.2, J1.1, J2.5, R3.2, R5.2, U1.5
LEDA: D1.1, R4.2
RO: J2.4, U1.1
VCC: C1.1, J2.2, R1.1, R4.1, U1.8

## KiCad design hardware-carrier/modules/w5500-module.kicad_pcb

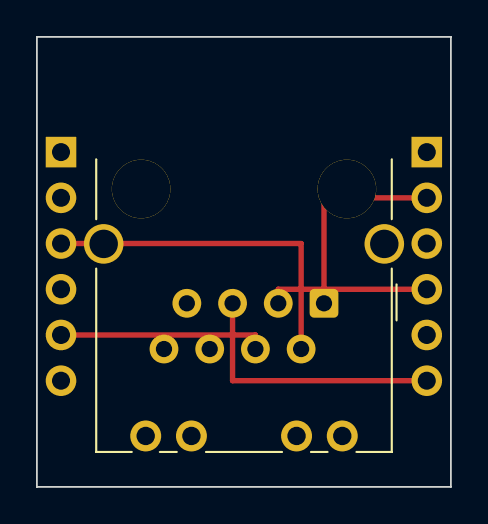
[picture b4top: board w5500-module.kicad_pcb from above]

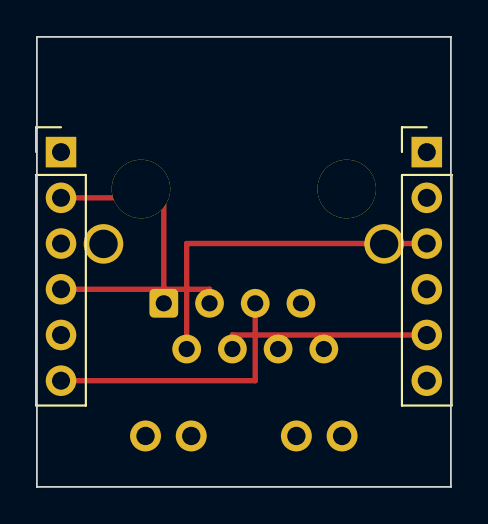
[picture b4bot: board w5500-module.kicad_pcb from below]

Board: 2 copper layers, 23.0 x 25.0 mm, 3 parts (2 on the bottom side), 6 nets.

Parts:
J1: J1; PinHeader_1x06_P2.54mm_Vertical
J2: J2; PinHeader_1x06_P2.54mm_Vertical
J3: J3; RJ45_Molex_9346520x_Horizontal

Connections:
TD1: J1.1, J2.1
TD2: J1.2, J2.2, J3.2
TD3: J1.3, J2.3, J3.3
TD4: J1.4, J2.4, J3.4
TD5: J1.5, J2.5, J3.5
TD6: J1.6, J2.6, J3.6

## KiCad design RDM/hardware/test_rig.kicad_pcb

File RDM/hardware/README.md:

# DMX/RDM bench test-rig carrier PCB

KiCad project for the socketed carrier described in [TEST_RIG_PCB.md](TEST_RIG_PCB.md).
It holds the bench modules in female headers (sockets) so the rig is solid, no breadboard.

The board is generated from a script so the wiring is the source of truth and can't drift.
`build_test_rig.py` places every part and assigns every net, then drops the parts in a
**staging grid, unplaced and unrouted on purpose** so you do the layout by hand. The
ratsnest shows every connection while you place, so it can't get miswired.

## Files

| File | What it is |
|---|---|
| `build_test_rig.py` | Generates `test_rig.kicad_pcb` + `.kicad_pro` + `test_rig_netlist.txt`. Edit here, not the board. |
| `test_rig.kicad_pcb` | The board: 18 footprints, 20 nets, staged, DRC-clean apart from the ratsnest. |
| `test_rig_netlist.txt` | Human-readable net list (ref.pad per net). Handy while routing. |
| `route_test_rig.py` | Autoroute with Freerouting once you've placed the parts (reuses the jar + JDK25 in `../../hardware/tools`). Width via `FR2_TRACK` env (default 1.0mm; 1.5mm also routes). Forces the width in the exported DSN. |
| `add_pin_silk.py` | Adds a function/GPIO silk label to every used pad on the placed board (1.0mm, offset ~5-6mm out). Run one footprint at a time in a fresh process (pcbnew's write path is flaky): `for r in J_PICOA J_PICOB ...; do python add_pin_silk.py $r; done`. |
| `gen_fab_test_rig.py` | Fab package: gerbers+drill zip, BOM, placement CSV. Refuses to emit anything while any net is unrouted. |
| `test_rig_gerbers.zip` | 2-layer gerbers + Excellon drill (AUX origin). Send this to the board house. |
| `test_rig_BOM.csv` / `test_rig_CPL.csv` | Buildable BOM + placement reference (this board is hand-assembled). |

Regenerate (KiCad 10 bundled python):

```bash
"/c/Program Files/KiCad/10.0/bin/python.exe" build_test_rig.py
```

## Parts on the board (reduced set)

Every part has a **function label on the silkscreen** (the Value field, on F.Silk) so
it's obvious what each one is, and the label moves with the part when you place it.

Sockets: RP2350 Pico Plus 2 W (2x 1x20), ESP32-S3-DevKitC-1 (2x 1x22), 2x MAX485
(2x 1x5 each, RXD/TXD variant, **cross-wired**), W5500 (2x5).

No jumpers: the MAX485 enable pins go straight to the MCU GPIOs (sim GP2, S3 GPIO8),
and all 5V pins tie to one rail. Power the whole rig from one USB (either board);
the other board runs off the shared rail. Plug both USB cables and they'll fight a
little (that's fine on a bench). Pico VBUS is left unconnected; it sources/sinks 5V
through VSYS. The W5500 runs off its 5V pin (its 3V3 pin is left NC).

Resistors, THT leaded so you can swap them by hand: bias `Rb1/Rb2` (~270R, A->+3V3 /
B->GND at the sim node) and the 2:1 ADC dividers `Rd1..Rd4` (10k, BUS_A->A1, BUS_B->A0).

Headers/connectors: measurement `J_MEAS` (`A B 3V3 GND 5V TX RX`), logic-analyzer
`J_LA` (2x8, signal row + full GND row), and `J_TERM`, a 3-pin screw terminal
(`A / B / GND`) for the DMX bus breakout.

**Left off** per request: external 5V input, power-good LEDs, decoupling caps, the
120R terminators, all jumpers (EN direction, 5V source select, W5500 3V3 select), and
the XLR. The SM712 TVS went with the XLR (it was the protection at that connector) —
say the word if you want any of these back.

## The lessons from the brief that are baked into the wiring

- **Cross-wired MAX485.** module RXD (RO) -> MCU RX, module TXD (DI) -> MCU TX, on
  both nodes. This is the swap that cost hours twice. The socket pin order runs
  bottom->top on the module (pad1 = GND, pad5 = EN), matched in the mapping.
- **Pico 3V3 from pin 36 (OUT), never pin 37 (3V3_EN).** pin 37 is left unconnected.
- **Bias at one node**, referenced to +3V3_SIM (the sim's 3.3V), A->3V3 / B->GND.
- **One common ground** (32 pads on GND) shared by both nodes, bias, dividers, breakout.
- Analog probe reads `BUS_A->A1 (GP27)`, `BUS_B->A0 (GP26)`, 2:1 divider, firmware x2.

Placement tip from the brief: keep the sim's GP0 (RX) and GP1 (TX) traces apart with a
ground trace between them, and keep each MAX485 close to its socket. Pour a solid ground
on both layers when you route.

## Routing + fab

Route by hand, or run `route_test_rig.py` to let Freerouting do the copper (GUI visible).
It routes at 1.5mm by default (`FR2_TRACK=0.8 ... route_test_rig.py` for thinner). Then
`gen_fab_test_rig.py` runs KiCad's DRC as a hard gate (0 unrouted or no output) and writes
`test_rig_gerbers.zip` + the BOM + placement CSV.

Build: order the bare 2-layer PCB from the gerber zip, solder the sockets / THT resistors /
pin headers / screw terminal, then plug the four modules into their sockets. It's a
hand-assembled bench board, no SMT.

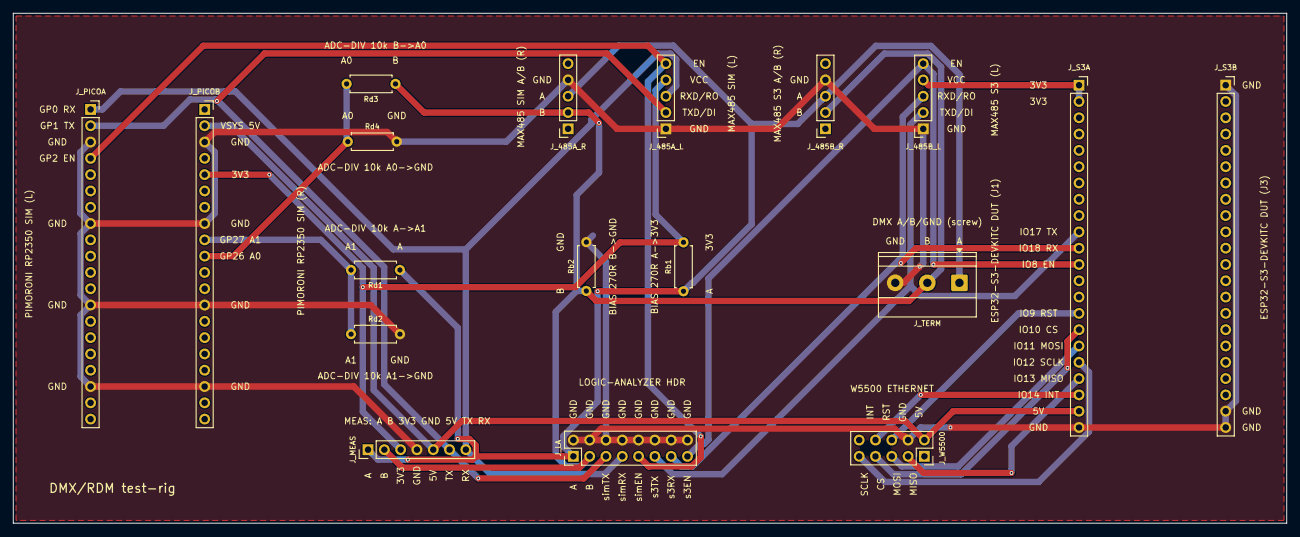
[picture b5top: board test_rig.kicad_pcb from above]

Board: 2 copper layers, 198.4 x 79.5 mm, 18 parts (0 on the bottom side), 20 nets.

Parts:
J_485A_L: MAX485 SIM (L); PinSocket_1x05_P2.54mm_Vertical
J_485A_R: MAX485 SIM A/B (R); PinSocket_1x05_P2.54mm_Vertical
J_485B_L: MAX485 S3 (L); PinSocket_1x05_P2.54mm_Vertical
J_485B_R: MAX485 S3 A/B (R); PinSocket_1x05_P2.54mm_Vertical
J_LA: LOGIC-ANALYZER HDR; PinHeader_2x08_P2.54mm_Vertical
J_MEAS: MEAS: A B 3V3 GND 5V TX RX; PinHeader_1x07_P2.54mm_Vertical
J_PICOA: PIMORONI RP2350 SIM (L); PinSocket_1x20_P2.54mm_Vertical
J_PICOB: PIMORONI RP2350 SIM (R); PinSocket_1x20_P2.54mm_Vertical
J_S3A: ESP32-S3-DEVKITC DUT (J1); PinSocket_1x22_P2.54mm_Vertical
J_S3B: ESP32-S3-DEVKITC DUT (J3); PinSocket_1x22_P2.54mm_Vertical
J_TERM: DMX A/B/GND (screw); TerminalBlock_Phoenix_MKDS-1,5-3_1x03_P5.00mm_Horizontal
J_W5500: W5500 ETHERNET; PinSocket_2x05_P2.54mm_Vertical
Rb1: BIAS 270R A->3V3; R_Axial_DIN0207_L6.3mm_D2.5mm_P7.62mm_Horizontal
Rb2: BIAS 270R B->GND; R_Axial_DIN0207_L6.3mm_D2.5mm_P7.62mm_Horizontal
Rd1: ADC-DIV 10k A->A1; R_Axial_DIN0207_L6.3mm_D2.5mm_P7.62mm_Horizontal
Rd2: ADC-DIV 10k A1->GND; R_Axial_DIN0207_L6.3mm_D2.5mm_P7.62mm_Horizontal
Rd3: ADC-DIV 10k B->A0; R_Axial_DIN0207_L6.3mm_D2.5mm_P7.62mm_Horizontal
Rd4: ADC-DIV 10k A0->GND; R_Axial_DIN0207_L6.3mm_D2.5mm_P7.62mm_Horizontal

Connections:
+3V3_S3: J_485B_L.4, J_S3A.1, J_S3A.2
+3V3_SIM: J_485A_L.4, J_MEAS.3, J_PICOB.5, Rb1.2
+5V: J_MEAS.5, J_PICOB.2, J_S3A.21, J_W5500.2
BUS_A: J_485A_R.3, J_485B_R.3, J_LA.1, J_MEAS.1, J_TERM.1, Rb1.1, Rd1.1
BUS_B: J_485A_R.2, J_485B_R.2, J_LA.3, J_MEAS.2, J_TERM.2, Rb2.1, Rd3.1
ETH_CS: J_S3A.16, J_W5500.7
ETH_INT: J_S3A.20, J_W5500.8
ETH_MISO: J_S3A.19, J_W5500.3
ETH_MOSI: J_S3A.17, J_W5500.5
ETH_RST: J_S3A.15, J_W5500.6
ETH_SCLK: J_S3A.18, J_W5500.9
GND: J_485A_L.1, J_485A_R.4, J_485B_L.1, J_485B_R.4, J_LA.2, J_LA.4, J_LA.6, J_LA.8, J_LA.10, J_LA.12, J_LA.14, J_LA.16, J_MEAS.4, J_PICOA.3, J_PICOA.8, J_PICOA.13, J_PICOA.18, J_PICOB.3, J_PICOB.8, J_PICOB.13, J_PICOB.18, J_S3A.22, J_S3B.1, J_S3B.21, J_S3B.22, J_TERM.3, J_W5500.4, Rb2.2, Rd2.2, Rd4.2
S3_DMX_EN: J_485B_L.5, J_LA.15, J_S3A.12
S3_DMX_RX: J_485B_L.3, J_LA.13, J_S3A.11
S3_DMX_TX: J_485B_L.2, J_LA.11, J_S3A.10
SIM_A0: J_PICOB.10, Rd3.2, Rd4.1
SIM_A1: J_PICOB.9, Rd1.2, Rd2.1
SIM_EN: J_485A_L.5, J_LA.9, J_PICOA.4
SIM_RX: J_485A_L.3, J_LA.7, J_MEAS.7, J_PICOA.1
SIM_TX: J_485A_L.2, J_LA.5, J_MEAS.6, J_PICOA.2

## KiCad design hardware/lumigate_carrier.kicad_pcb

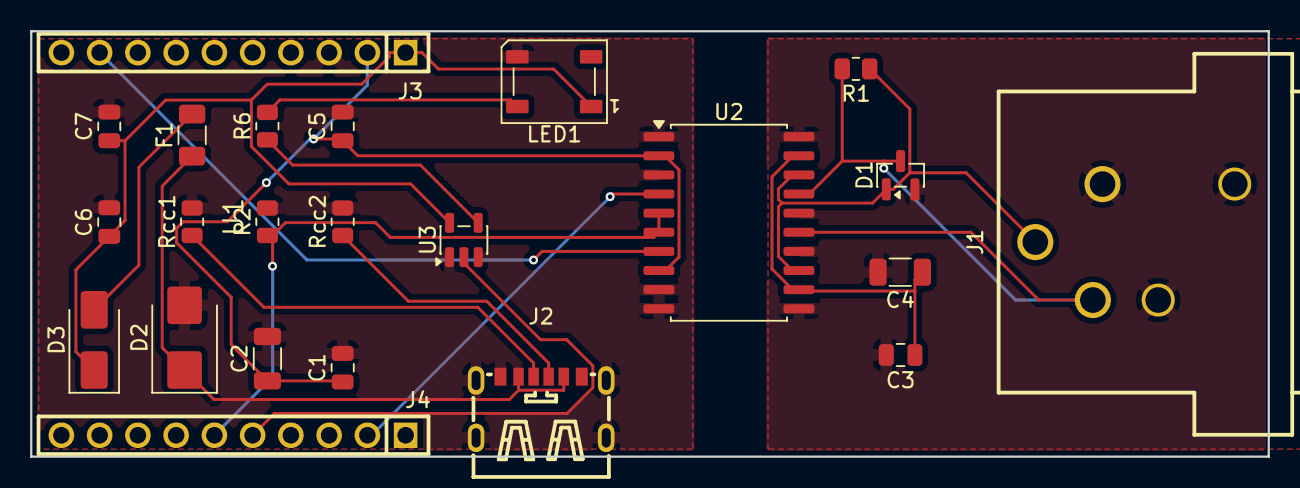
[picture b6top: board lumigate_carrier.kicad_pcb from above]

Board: 2 copper layers, 82.2 x 28.2 mm, 24 parts (0 on the bottom side), 17 nets.

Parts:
C1, C3, C5, C6, C7: C_0805_2012Metric
C2, C4: C_1206_3216Metric
D1: SOT-23
D2: D_SMB
D3: D_SMA
F1: Fuse_1206_3216Metric
J1: XLR-3 DMX out (XLR-328P); CONN-TH_XLR-328P
J2: USB-C 6P power (TYPE-C 6P); TYPE-C-SMD_TYPE-C-6P_1
J3, J4: 1x10 socket 2.54 (C35445); HDR-TH_10P-P2.54-V-F
LED1: LED_WS2812B_PLCC4_5.0x5.0mm_P3.2mm
R1, R2, R6: R_0805_2012Metric
Rcc1, Rcc2: R_0805_2012Metric
U1: ESP32-POE-ISO module (plug-in)
U2: SOIC-20W_7.5x12.8mm_P1.27mm
U3: SOT-23-5

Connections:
+3V3: C1.1, C2.1, C5.1, J3.2, U2.2, U2.8
+5V: C6.1, C7.1, D3.1, J3.1, LED1.1, U3.5
CC1: J2.A5, Rcc1.1
CC2: J2.B5, Rcc2.1
DMX_A: D1.1, J1.3, R1.1, U2.13, U2.18
DMX_B: D1.3, J1.2, R1.2, U2.15, U2.17
DMX_EN: J4.6, R2.1, U2.5, U2.6
DMX_RX: J4.2, U2.4
DMX_TX: J3.9, U2.7
GND: C1.2, C2.2, C5.2, C6.2, C7.2, D2.2, J2.7, J2.A12, J2.B12, J3.3, LED1.3, R2.2, Rcc1.2, Rcc2.2, U2.1, U2.3, U2.9, U2.10, U3.1, U3.3
GNDISO: C3.2, C4.2, D1.2, J1.1, U2.11, U2.14, U2.16, U2.20
LED_DIN: LED1.4, R6.2
RGB_DIN: J4.5, U3.2
RGB_DIN_5V: R6.1, U3.4
VBUS_C: D2.1, F1.1, J2.A9, J2.B9
VBUS_FUSED: D3.2, F1.2
VISO: C3.1, C4.1, U2.12, U2.19

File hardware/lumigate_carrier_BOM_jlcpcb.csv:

Comment,Designator,Footprint,LCSC Part #,Type
100nF,"C1,C3,C5,C6,C7",C_0805_2012Metric,C49678,SMT/Assembly
10uF,"C2,C4",C_1206_3216Metric,C13585,SMT/Assembly
SM712,D1,SOT-23,C404012,SMT/Assembly
SMAJ5.0A,D2,D_SMB,C87074,SMT/Assembly
SS34,D3,D_SMA,C8678,SMT/Assembly
PTC 1A 1206,F1,Fuse_1206_3216Metric,C70082,SMT/Assembly
XLR-3 female RA (XLR-328P),J1,CONN-TH_XLR-328P,C309326,SMT/Assembly
USB-C 6P power (TYPE-C 6P),J2,TYPE-C-SMD_TYPE-C-6P_1,C456012,SMT/Assembly
1x10 socket 2.54 (C35445),"J3,J4",HDR-TH_10P-P2.54-V-F,C35445,SMT/Assembly
WS2812B,LED1,LED_WS2812B_PLCC4_5.0x5.0mm_P3.2mm,C2761795,SMT/Assembly
120R,R1,R_0805_2012Metric,C17437,SMT/Assembly
10k,R2,R_0805_2012Metric,C17414,SMT/Assembly
330R,R6,R_0805_2012Metric,C17630,SMT/Assembly
5k1,"Rcc1,Rcc2",R_0805_2012Metric,C27834,SMT/Assembly
ADM2587EBRWZ,U2,SOIC-20W_7.5x12.8mm_P1.27mm,C12081,SMT/Assembly
74LVC1G125,U3,SOT-23-5,C23654,SMT/Assembly

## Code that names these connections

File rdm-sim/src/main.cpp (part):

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
// ---------------------------------------------------------------------------
// Pins - this is the SIMULATOR board, wired to its own MAX485. Tie the MAX485's
// DE and /RE together and drive them from SIM_EN_PIN (HIGH = transmit).
// ---------------------------------------------------------------------------
#ifndef SIM_TX_PIN
#define SIM_TX_PIN   17    // -> MAX485 DI
#endif
#ifndef SIM_RX_PIN
#define SIM_RX_PIN   18    // <- MAX485 RO
#endif
#ifndef SIM_EN_PIN
#define SIM_EN_PIN    8    // -> MAX485 DE + /RE (tied together)
#endif
#ifndef RGB_LED_PIN
#define RGB_LED_PIN  48    // ESP32-S3-DevKitC-1 onboard WS2812 (some boards: 38)
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        {3, "RGB"},
    };
    dmx_driver_install(DMX_PORT, &config, personalities, 2);
    dmx_set_pin(DMX_PORT, SIM_TX_PIN, SIM_RX_PIN, SIM_EN_PIN);

    rdm_register_identify_device(DMX_PORT, onIdentify, NULL);
    rdm_register_device_label(DMX_PORT, "LumiGate RDM Sim", NULL, NULL);
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    dmx_set_mab_len(DMX_PORT, g_mabUs);

    Serial.printf("[sim] ready: port=%d tx=%d rx=%d en=%d led=%d\n",
                  DMX_PORT, SIM_TX_PIN, SIM_RX_PIN, SIM_EN_PIN, RGB_LED_PIN);
}

void loop() {
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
